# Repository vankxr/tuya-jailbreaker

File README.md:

# tuya-jailbreaker
This small module aims to replace the original Wi-Fi module present in Tuya/Elivco smart plugs. The pin connections were reverse engineered from the base PCB traces, and the pad dimensions/spacing was measured from the original module.

## Pictures
The original module in blue, the ESP8285 module in green.

## Hardware
These modules are kind of impossible to disassemble without leaving some marks behind. Fortunately, after almost destroying the case of the first one I disassembled, I was able to figure out how they are put together and further teardowns were much easier.
Basically the trick is to drill three very small holes, and prying the two parts apart with a small screwdriver inserted into the holes. One hole for each side of the case, the side that has the push-button should not have a hole.
After hearing a click sound, the two parts can easily be separated, taking care not to rip apart the Earth connection.

Re-assembly is then performed by attaching everything and filling the previously mentioned holes with hot glue.

TODO: Add pictures

## Software
The jailbreaker was flashed with [Tasmota](https://tasmota.github.io/docs/), and it was configured with the correct pinout for the Energy Metering IC that is present in the base PCB.

## Tasmota configuration
The first module I ordered back in June 2021 used the BL0937 energy metering IC, so naturally I designed this PCB taking this insto account after figuring out the pinout.
Later though, I ordered more modules, and realised they were slightly different. Modules ordered in November 2021 came with the BL0942 energy metering IC, which seems to be better since it does not require calibration. Even though I only figured this out after removing the original module and installing a jailbreak module, I was able to figure out which pins are connected to the energy metering IC and fortunately everything worked after configuring them correctly. Below are screenshots of Tasmota configuration for both versions of the base PCB.
### v1 (version with BL0937)

### v2 (version with BL0942)

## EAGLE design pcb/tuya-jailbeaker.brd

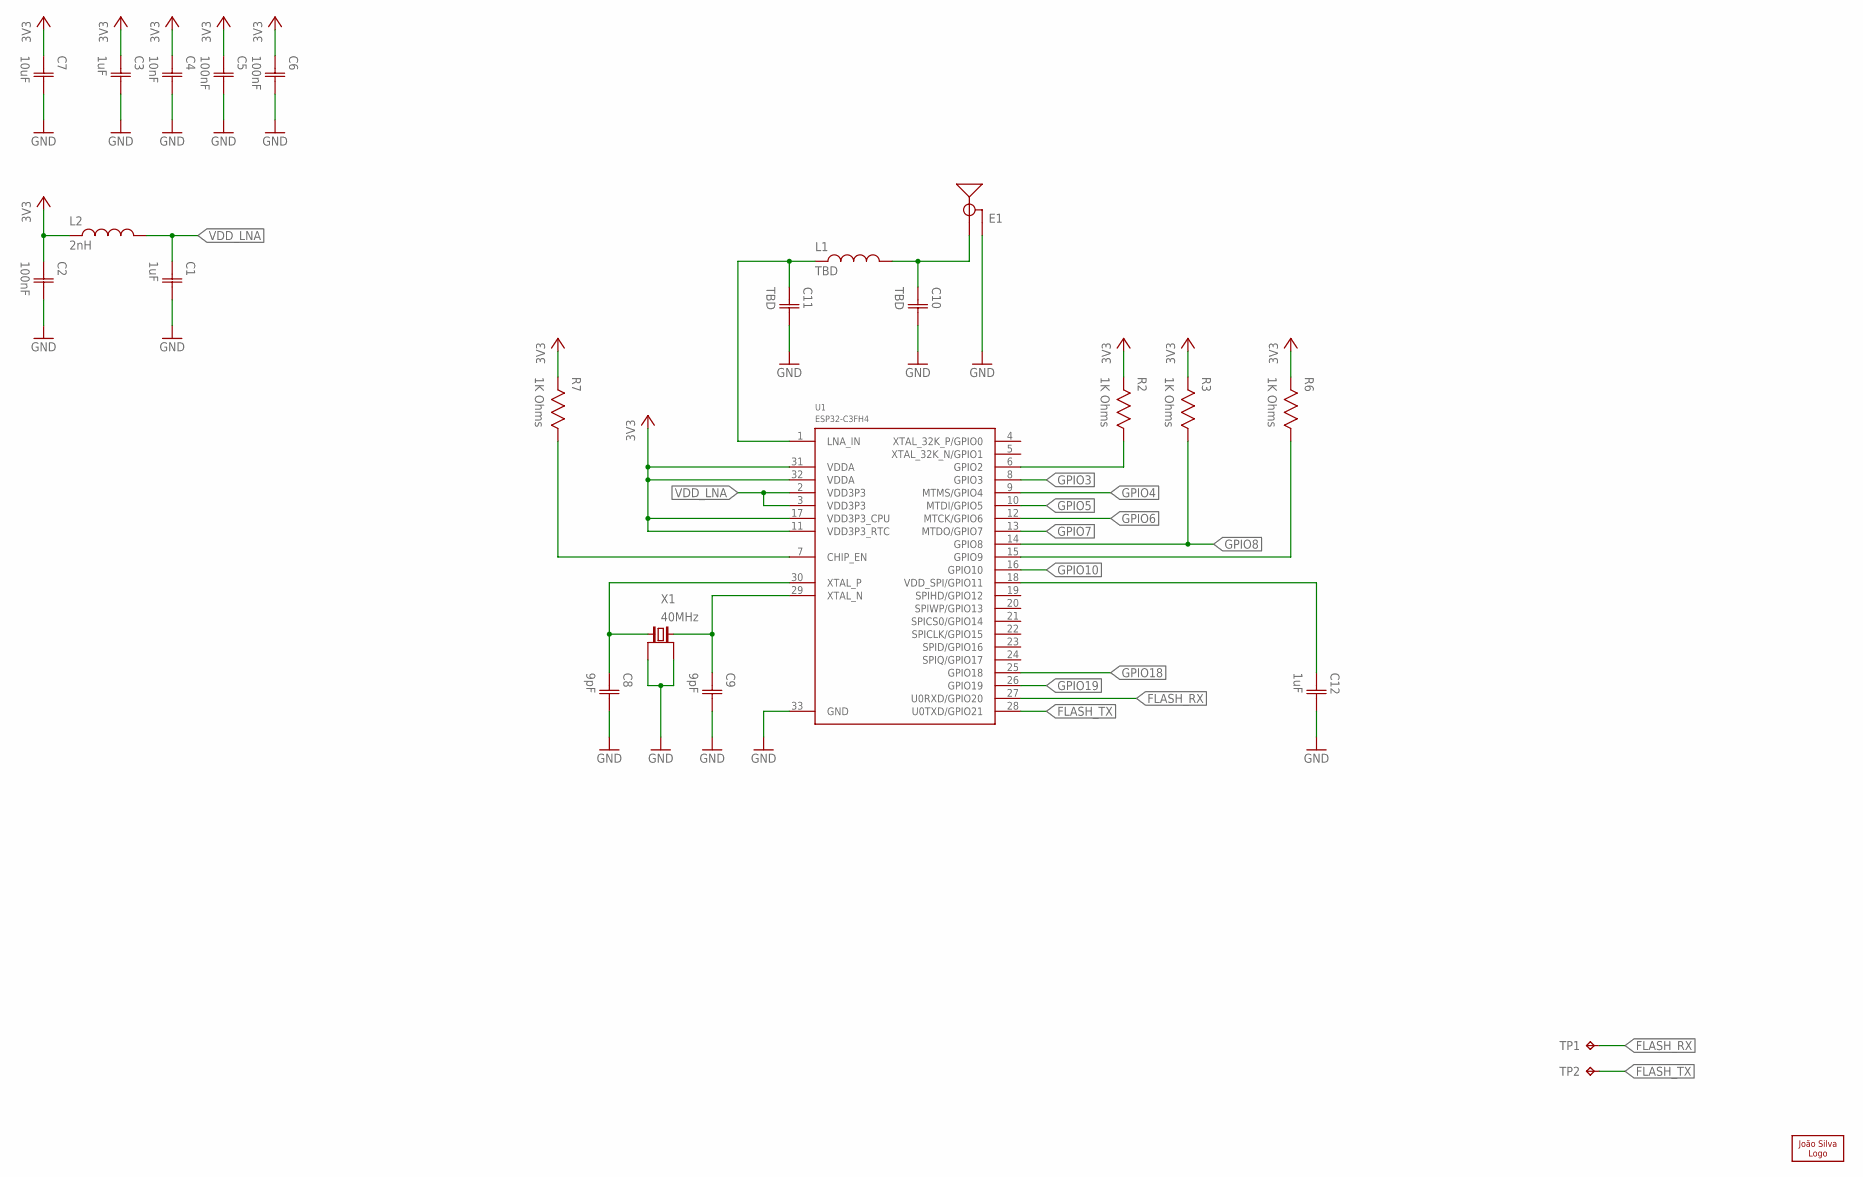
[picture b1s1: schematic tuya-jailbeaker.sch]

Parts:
C1, C3, C12: 1uF; CAP0402
C2, C5, C6: 100nF; CAP0402
C4: 10nF; CAP0402
C7: 10uF; CAP0603
C8, C9: 9pF; CAP0402
C10, C11: TBD; CAP0402
E1: 2.4GHZ; OLIMEX_ANT_ESP8266_ANT
L1: TBD; IND0402
L2: 2nH; IND0402
LOGO1: JS-5MM; JS_5MM
R2, R3, R6, R7: 1K Ohms; RES0402
TP1, TP2: TESTPOINT-1.27MM; PAD1.27MM
U1: ESP32-C3FH4; QFN32
X1: 40MHz; 4-SMD-2520

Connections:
3V3: C2.1 (C1), C3.1 (C1), C4.1 (C1), C5.1 (C1), C6.1 (C1), C7.1 (C1), L2.1, R2.2, R3.2, R6.2, R7.2, U1.11 (VDD3P3_RTC), U1.17 (VDD3P3_CPU), U1.31 (VDDA), U1.32 (VDDA)
ANT: C10.1 (C1), E1.ANT (SIGNAL), L1.2
CEN: R7.1, U1.7 (CHIP_EN)
FLASH_RX: TP1.TP, U1.27 (U0RXD/GPIO20)
FLASH_TX: TP2.TP, U1.28 (U0TXD/GPIO21)
GND: C1.2 (C2), C2.2 (C2), C3.2 (C2), C4.2 (C2), C5.2 (C2), C6.2 (C2), C7.2 (C2), C8.2 (C2), C9.2 (C2), C10.2 (C2), C11.2 (C2), C12.2 (C2), E1.GND, U1.33 (GND), X1.2 (GND), X1.4 (GND)
GPIO2: R2.1, U1.6 (GPIO2)
GPIO3: U1.8 (GPIO3)
GPIO4: U1.9 (MTMS/GPIO4)
GPIO5: U1.10 (MTDI/GPIO5)
GPIO6: U1.12 (MTCK/GPIO6)
GPIO7: U1.13 (MTDO/GPIO7)
GPIO8: R3.1, U1.14 (GPIO8)
GPIO9: R6.1, U1.15 (GPIO9)
GPIO10: U1.16 (GPIO10)
GPIO18: U1.25 (GPIO18)
GPIO19: U1.26 (GPIO19)
LNA_IN: C11.1 (C1), L1.1, U1.1 (LNA_IN)
VDD_LNA: C1.1 (C1), L2.2, U1.2 (VDD3P3), U1.3 (VDD3P3)
VDD_SPI: C12.1 (C1), U1.18 (VDD_SPI/GPIO11)
XTALN: C9.1 (C1), U1.29 (XTAL_N), X1.1 (2)
XTALP: C8.1 (C1), U1.30 (XTAL_P), X1.3 (1)

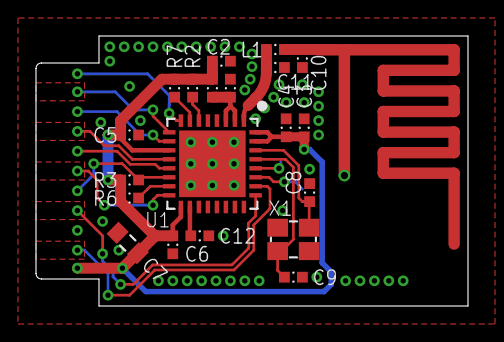
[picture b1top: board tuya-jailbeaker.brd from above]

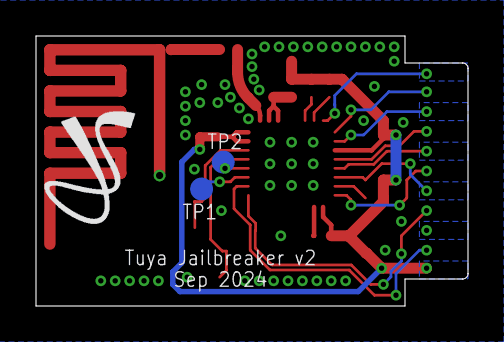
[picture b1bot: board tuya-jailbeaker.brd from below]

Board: 2 copper layers, 24.0 x 15.0 mm, 24 parts (3 on the bottom side), 14 nets.

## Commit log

2021-06-03 Add logo Generate schematic PDF
2021-07-07 Add some pictures
2021-07-07 Add tasmota picture
2021-07-07 Add plug pictures
2022-01-06 Add Tasmota configuration for Tuya v1 and v2
2025-05-19 Update to ESP32-C3
